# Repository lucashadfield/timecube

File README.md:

# timecube
> e-ink pomodoro timer

[Time Cube.webm](https://user-images.githubusercontent.com/12473153/235540202-a3ebf8da-60be-4fac-9890-19129da23939.webm)

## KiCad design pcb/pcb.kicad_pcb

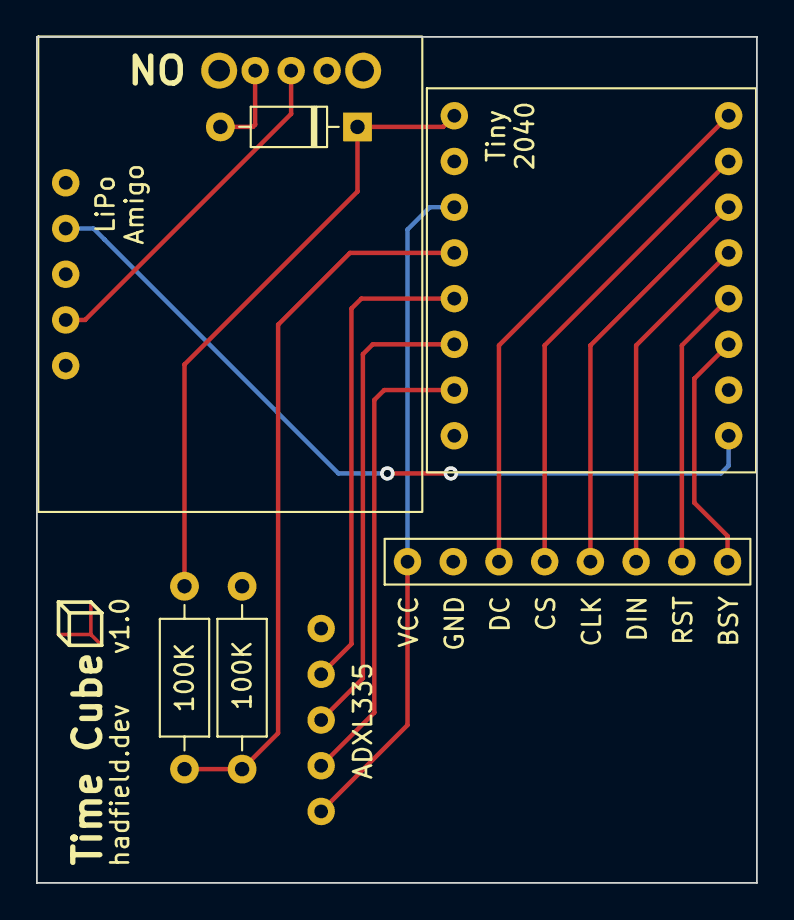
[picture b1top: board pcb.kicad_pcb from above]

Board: 2 copper layers, 40.0 x 47.0 mm, 8 parts (0 on the bottom side), 16 nets.

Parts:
D1: 1N5712; D_DO-35_SOD27_P7.62mm_Horizontal
R1, R2: 100K; R_Axial_DIN0207_L6.3mm_D2.5mm_P10.16mm_Horizontal
SW1: SW_SPDT; Switch
U1: Pimoroni_LiPo_Amigo; LiPo Amigo
U2: Timecube_Accelerometer; ADXL335
U3: Tiny2040
U5: E-ink_Driver; Driver Data

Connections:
/GND: R2.2, U1.5 (GND), U2.5 (GND), U3.2 (GND), U3.8 (GND), U5.2 (GND)
/VCC: U2.1 (VCC), U3.3 (3V3), U5.1 (VCC)
unnamed: D1.1 (K), R1.1, U3.1 (VBUS)
unnamed: D1.2 (A), SW1.3 (C)
unnamed: R1.2, R2.1, U3.4 (GP29)
unnamed: SW1.2 (B), U1.4 (VBAT)
unnamed: U1.2 (5V), U3.9 (GP7)
unnamed: U2.3 (Y), U3.6 (GP27)
unnamed: U2.4 (Z), U3.5 (GP28)
unnamed: U2.2 (X), U3.7 (GP26)
unnamed: U3.11 (GP5), U5.8 (BUSY)
unnamed: U3.12 (GP4), U5.7 (RST)
unnamed: U3.13 (GP3), U5.6 (DIN)
unnamed: U3.14 (GP2), U5.5 (CLK)
unnamed: U3.15 (GP1), U5.4 (CS)
unnamed: U3.16 (GP0), U5.3 (DC)

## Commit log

2021-07-20 basic version with keyboard input
2021-07-21 refactored logic
2021-07-21 refactored
2021-07-22 periodic logging
2021-07-22 added options to change config based on input
2022-05-08 basic functionality running on hardware
2022-05-08 next interval symbol
2022-08-29 pcb 0.3, inner v4, flash_files update
2022-08-29 cleanup
2022-08-29 v0.1
2022-09-03 v0.2.0
2022-09-04 pcb updates for 1.0
2022-09-04 readme
2022-09-05 Add LICENSE
2023-04-24 fp info cache
2023-04-30 update font to add pause and arrow symbols
2023-04-30 fix offsets
2023-05-07 update duration
